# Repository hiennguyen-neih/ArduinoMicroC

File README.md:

# ArduinoMicroC
Arduino Micro-C

Schematic design and PCB layout for Arduino Pro Micro with USB type C connector.

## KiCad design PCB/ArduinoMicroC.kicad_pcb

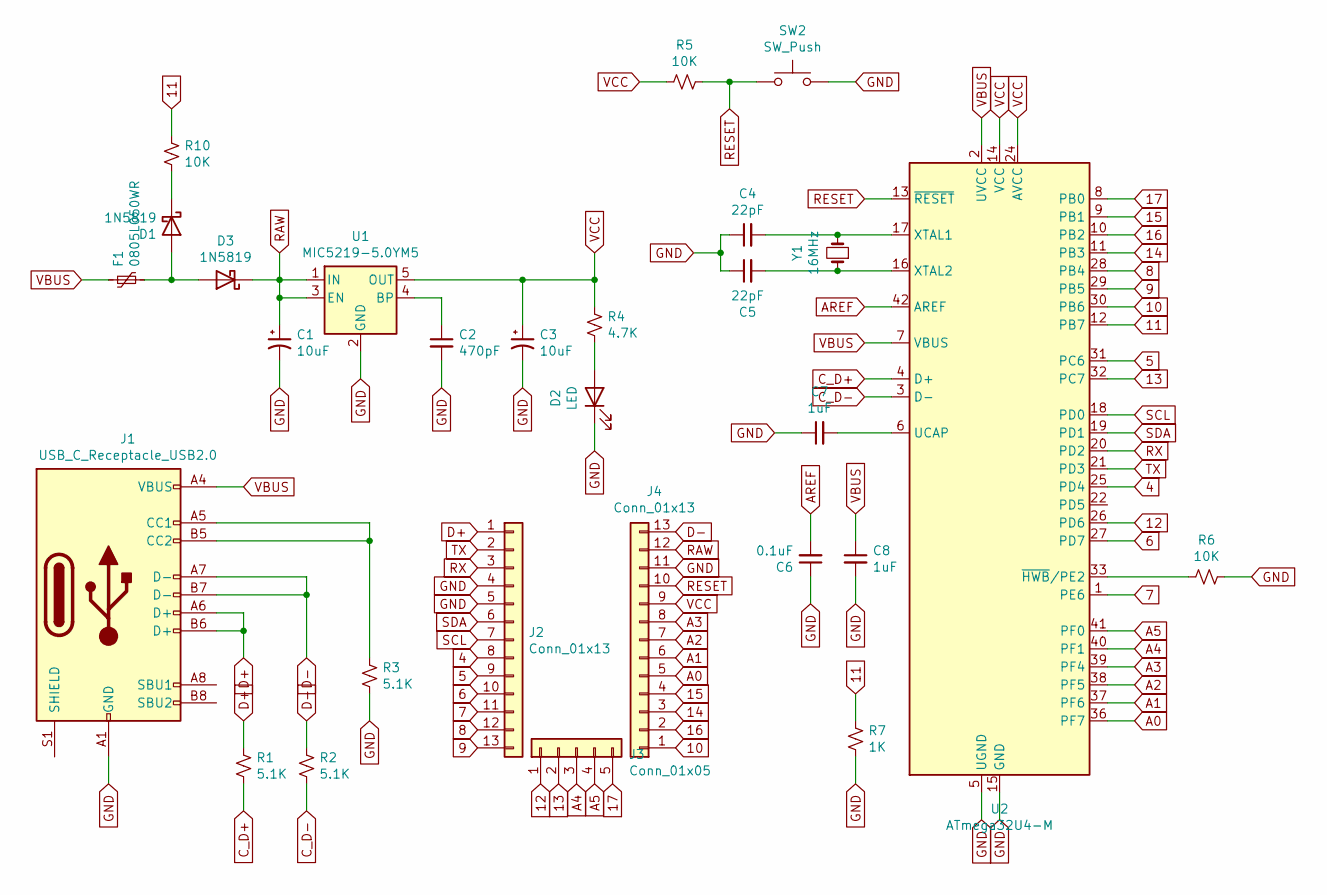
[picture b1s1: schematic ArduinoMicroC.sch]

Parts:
C1, C3: 10uF; CP_EIA-2012-15_AVX-P
C2: 470pF; C_0402_1005Metric
C4, C5: 22pF; C_0402_1005Metric
C6: 0.1uF; C_0402_1005Metric
C7, C8: 1uF; C_0402_1005Metric
D1, D3: 1N5819; D_SOD-123F
D2: LED; LED_0402_1005Metric
F1: 0805L050WR; Fuse_0805_2012Metric
J1: USB_C_Receptacle_USB2.0; USB_C_Receptacle_HRO_TYPE-C-31-M-12
J2, J4: Conn_01x13; PinHeader_1x13_P2.54mm_Circular_Vertical_2
J3: Conn_01x05; PinHeader_1x05_P2.54mm_Circular_Vertical_2
R1, R2, R3: 5.1K; R_0201_0603Metric
R4: 4.7K; R_0201_0603Metric
R5, R6, R10: 10K; R_0201_0603Metric
R7: 1K; R_0201_0603Metric
SW2: SW_Push; SW_Push_SPST_NO_Alps_SKRK
U1: MIC5219-5.0YM5; SOT-23-5
U2: ATmega32U4-M; QFN-44-1EP_7x7mm_P0.5mm_EP5.2x5.2mm
Y1: 16MHz; Crystal_SMD_5032-2Pin_5.0x3.2mm

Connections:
4: J2.8, U2.25 (PD4)
5: J2.9, U2.31 (PC6)
6: J2.10, U2.27 (PD7)
7: J2.11, U2.1 (PE6)
8: J2.12, U2.28 (PB4)
9: J2.13, U2.29 (PB5)
10: J4.1, U2.30 (PB6)
11: R7.1, R10.1, U2.12 (PB7)
12: J3.1, U2.26 (PD6)
13: J3.2, U2.32 (PC7)
14: J4.3, U2.11 (PB3)
15: J4.4, U2.9 (PB1)
16: J4.2, U2.10 (PB2)
17: J3.5, U2.8 (PB0)
A0: J4.5, U2.36 (PF7)
A1: J4.6, U2.37 (PF6)
A2: J4.7, U2.38 (PF5)
A3: J4.8, U2.39 (PF4)
A4: J3.3, U2.40 (PF1)
A5: J3.4, U2.41 (PF0)
AREF: C6.2, U2.42 (AREF)
C_D+: R1.2, U2.4 (D+)
C_D-: R2.2, U2.3 (D-)
D+: J1.A6 (D+), J1.B6 (D+), J2.1, R1.1
D-: J1.A7 (D-), J1.B7 (D-), J4.13, R2.1
GND: C1.2, C2.2, C3.2, C4.1, C5.1, C6.1, C7.1, C8.2, D2.1 (K), J1.A1 (GND), J1.A12 (GND), J1.B1 (GND), J1.B12 (GND), J2.4, J2.5, J4.11, R3.2, R6.2, R7.2, SW2.2, U1.2 (GND), U2.5 (UGND), U2.15 (GND), U2.23 (GND), U2.35 (GND), U2.43 (GND), U2.45 (GND)
unnamed: C2.1, U1.4 (BP)
unnamed: C4.2, U2.17 (XTAL1), Y1.2
unnamed: C5.2, U2.16 (XTAL2), Y1.1
unnamed: C7.2, U2.6 (UCAP)
unnamed: D1.1 (K), R10.2
unnamed: D1.2 (A), D3.2 (A), F1.2
unnamed: D2.2 (A), R4.2
unnamed: J1.A5 (CC1), J1.B5 (CC2), R3.1
unnamed: R6.1, U2.33 (~HWB~/PE2)
RAW: C1.1, D3.1 (K), J4.12, U1.1 (IN), U1.3 (EN)
RESET: J4.10, R5.2, SW2.1, U2.13 (~RESET)
RX: J2.3, U2.20 (PD2)
SCL: J2.7, U2.18 (PD0)
SDA: J2.6, U2.19 (PD1)
TX: J2.2, U2.21 (PD3)
VBUS: C8.1, F1.1, J1.A4 (VBUS), J1.A9 (VBUS), J1.B4 (VBUS), J1.B9 (VBUS), U2.2 (UVCC), U2.7 (VBUS)
VCC: C3.1, J4.9, R4.1, R5.1, U1.5 (OUT), U2.14 (VCC), U2.24 (AVCC), U2.34 (VCC), U2.44 (AVCC)

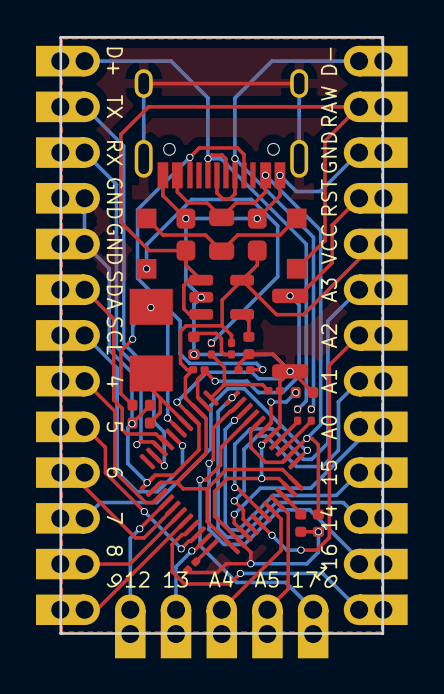
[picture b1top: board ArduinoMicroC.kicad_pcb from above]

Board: 2 copper layers, 17.9 x 33.1 mm, 28 parts (0 on the bottom side), 43 nets.

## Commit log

2020-12-06 First version of PCB
2020-12-06 Generate Gerber files
2020-12-07 Hide Reference and Value of components
2020-12-07 Add label into headers
2020-12-12 Update SilkS layer
2020-12-12 Create module sympol and footprints
2020-12-12 Remove all SilkS layer of components
2021-01-01 Second version of PCB
    - Make D11 pin is USB check pin only.
    - Remove D11 out of GPIO headers.
    - Remove TX LED and RX LED.
    - Smaller PCB with 29 pins instead of 30 pins.
    - Fix the USB check diode.
    - Add a Resistor to GND in D11 pin.
2021-01-28 Make zone outline for USB Sheld and update module library and footprint for new version
2021-02-03 Update Schematic for version 3
    Add D+ and D- pins for headers
2021-02-03 Update device modules in PCB for version 3
2021-02-09 Update PCB for version 3
2021-02-09 Update Text for PCB
2021-02-10 Add filled zones for PCB
2021-02-10 Update header J2, J4 and update filled zones
2021-02-10 Update Gerber files
2021-02-16 Update headers for PCB
